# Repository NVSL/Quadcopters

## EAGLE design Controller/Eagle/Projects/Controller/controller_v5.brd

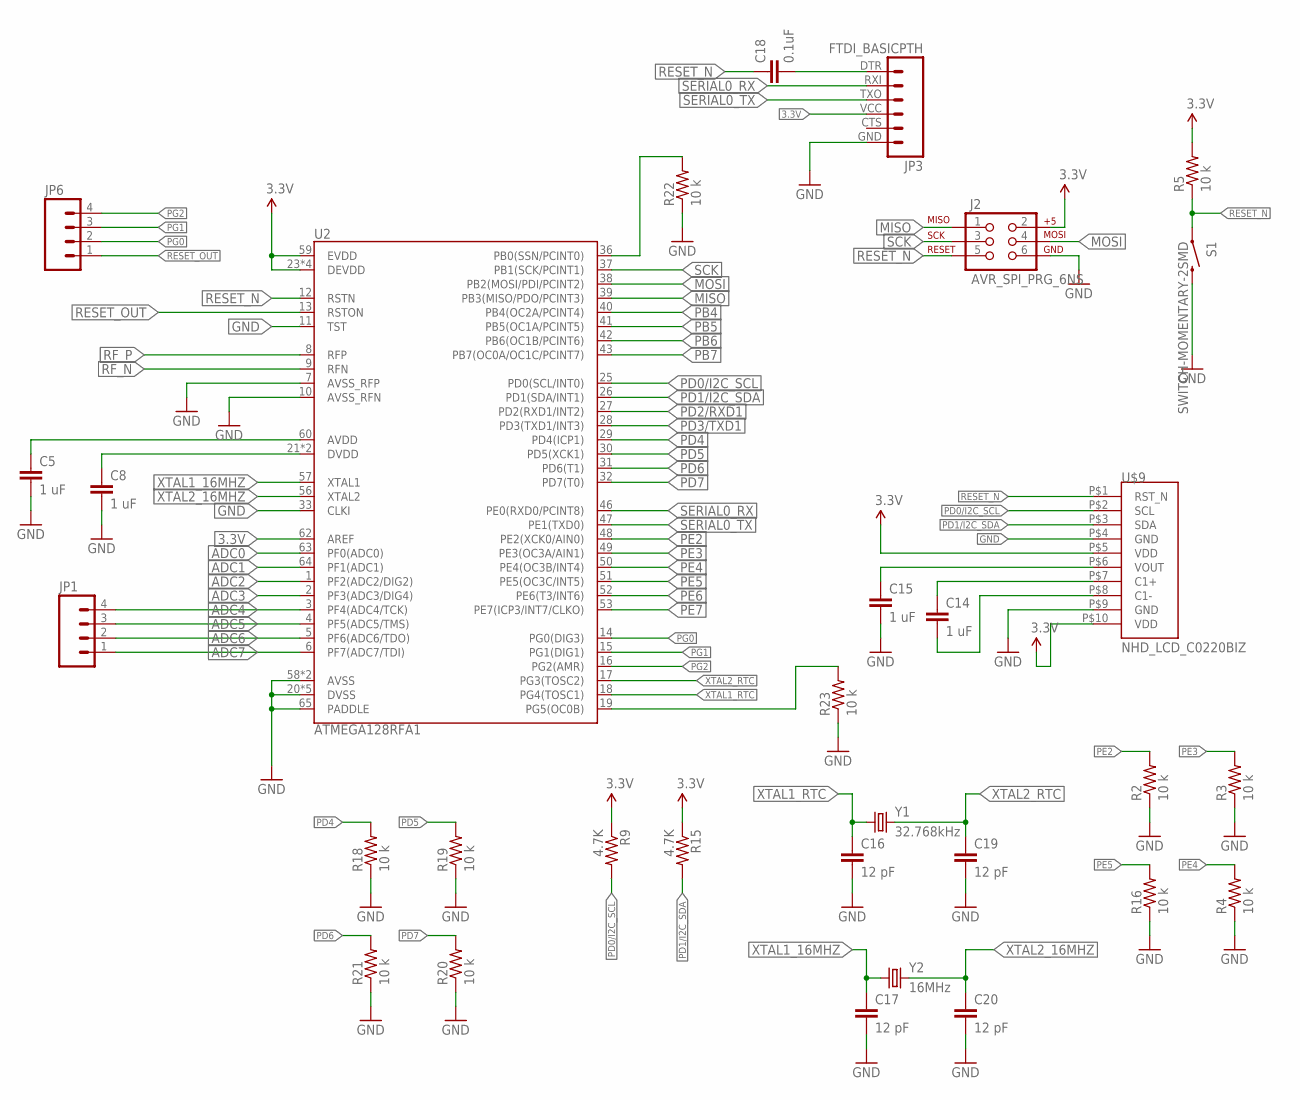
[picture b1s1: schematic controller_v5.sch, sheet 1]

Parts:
C5, C8, C14, C15: 1 uF; 0805
C16, C17, C19, C20: 12 pF; 0805
C18: 0.1uF; 0805
J2: AVR_SPI_PRG_6NS; 2X3-NS
JP1, JP6: M04PTH; 1X04
JP3: FTDI_BASICPTH; FTDI_BASIC
R2, R3, R4, R5, R16, R18, R19, R20, R21, R22, R23: 10 k; 0805
R9, R15: 4.7K; 0805
S1: SWITCH-MOMENTARY-2SMD; TACTILE_SWITCH_SMD
U2: ATMEGA128RFA1; QFN-64
U$9: NHD_LCD_C0220BIZ; 1X08-2MMPTH-LCD
Y1: 32.768kHz; CRYSTAL-32KHZ-SMD
Y2: 16MHz; CRYSTAL-SMD-5X3

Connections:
ADC0: U2.63 (PF0(ADC0)); also elsewhere on the board
ADC1: U2.64 (PF1(ADC1)); also elsewhere on the board
ADC2: U2.1 (PF2(ADC2/DIG2)); also elsewhere on the board
ADC3: U2.2 (PF3(ADC3/DIG4)); also elsewhere on the board
ADC4: JP1.4, U2.3 (PF4(ADC4/TCK))
ADC5: JP1.3, U2.4 (PF5(ADC5/TMS))
ADC6: JP1.2, U2.5 (PF6(ADC6/TDO))
ADC7: JP1.1, U2.6 (PF7(ADC7/TDI))
GND: C5.2, C8.2, C15.2, C16.2, C17.2, C19.2, C20.2, J2.6, JP3.GND (6), R2.1, R3.1, R4.1, R16.1, R18.1, R19.1, R20.1, R21.1, R22.1, R23.1, S1.3 (2), U2.7 (AVSS_RFP), U2.10 (AVSS_RFN), U2.11 (TST), U2.20 (DVSS), U2.24 (DVSS), U2.33 (CLKI), U2.35 (DVSS), U2.45 (DVSS), U2.55 (DVSS), U2.58 (AVSS), U2.61 (AVSS), U2.65 (PADDLE), U$9.P$4 (GND), U$9.P$9 (GND); also elsewhere on the board
MISO: J2.1, U2.39 (PB3(MISO/PDO/PCINT3))
MOSI: J2.4, U2.38 (PB2(MOSI/PDI/PCINT2))
unnamed: C18.2, JP3.DTR (1)
unnamed: C14.1, U$9.P$7 (C1+)
unnamed: C5.1, U2.60 (AVDD)
unnamed: C8.1, U2.21 (DVDD), U2.22 (DVDD)
unnamed: C14.2, U$9.P$8 (C1-)
PB0: R22.2, U2.36 (PB0(SSN/PCINT0))
PB1: R23.2, U2.19 (PG5(OC0B))
PB4: U2.40 (PB4(OC2A/PCINT4)); also elsewhere on the board
PB5: U2.41 (PB5(OC1A/PCINT5)); also elsewhere on the board
PB6: U2.42 (PB6(OC1B/PCINT6)); also elsewhere on the board
PB7: U2.43 (PB7(OC0A/OC1C/PCINT7)); also elsewhere on the board
PD0/I2C_SCL: R9.2, U2.25 (PD0(SCL/INT0)), U$9.P$2 (SCL)
PD1/I2C_SDA: R15.2, U2.26 (PD1(SDA/INT1)), U$9.P$3 (SDA)
PD2/RXD1: U2.27 (PD2(RXD1/INT2)); also elsewhere on the board
PD3/TXD1: U2.28 (PD3(TXD1/INT3)); also elsewhere on the board
PD4: R18.2, U2.29 (PD4(ICP1))
PD5: R19.2, U2.30 (PD5(XCK1))
PD6: R21.2, U2.31 (PD6(T1))
PD7: R20.2, U2.32 (PD7(T0))
PE2: R2.2, U2.48 (PE2(XCK0/AIN0))
PE3: R3.2, U2.49 (PE3(OC3A/AIN1))
PE4: R4.2, U2.50 (PE4(OC3B/INT4))
PE5: R16.2, U2.51 (PE5(OC3C/INT5))
PE6: U2.52 (PE6(T3/INT6)); also elsewhere on the board
PE7: U2.53 (PE7(ICP3/INT7/CLKO)); also elsewhere on the board
PG0: JP6.2, U2.14 (PG0(DIG3))
PG1: JP6.3, U2.15 (PG1(DIG1))
PG2: JP6.4, U2.16 (PG2(AMR))
RESET_N: C18.1, J2.5, R5.1, S1.1, U2.12 (RSTN), U$9.P$1 (RST_N)
RESET_OUT: JP6.1, U2.13 (RSTON)
RF_N: U2.9 (RFN); also elsewhere on the board
RF_P: U2.8 (RFP); also elsewhere on the board
SCK: J2.3, U2.37 (PB1(SCK/PCINT1))
SERIAL0_RX: JP3.RXI (2), U2.46 (PE0(RXD0/PCINT8))
SERIAL0_TX: JP3.TXO (3), U2.47 (PE1(TXD0))
VOUT: C15.1, U$9.P$6 (VOUT)
XTAL1_16MHZ: C17.1, U2.57 (XTAL1), Y2.1
XTAL1_RTC: C16.1, U2.18 (PG4(TOSC1)), Y1.X1 (1)
XTAL2_16MHZ: C20.1, U2.56 (XTAL2), Y2.3 (2)
XTAL2_RTC: C19.1, U2.17 (PG3(TOSC2)), Y1.X2 (2)

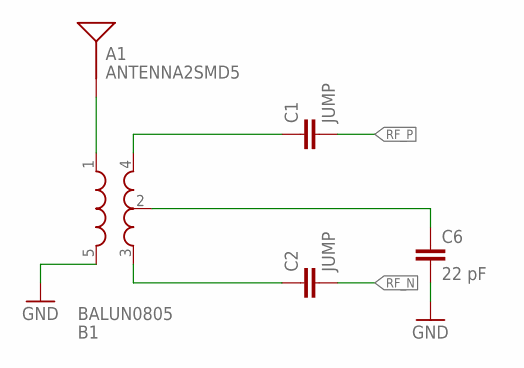
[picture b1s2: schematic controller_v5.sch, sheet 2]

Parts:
A1: ANTENNA2SMD5; ANTENNA-CHIP5
B1: BALUN0805; BALUN
C1, C2: JUMP; 0805
C6: 22 pF; 0805

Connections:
GND: B1.5 (GND), C6.2; also elsewhere on the board
unnamed: B1.4 (OUT1), C1.1
unnamed: B1.3 (OUT2), C2.1
unnamed: B1.2 (GND), C6.1
unnamed: A1.FEED, B1.1 (IN)
RF_N: C2.2; also elsewhere on the board
RF_P: C1.2; also elsewhere on the board

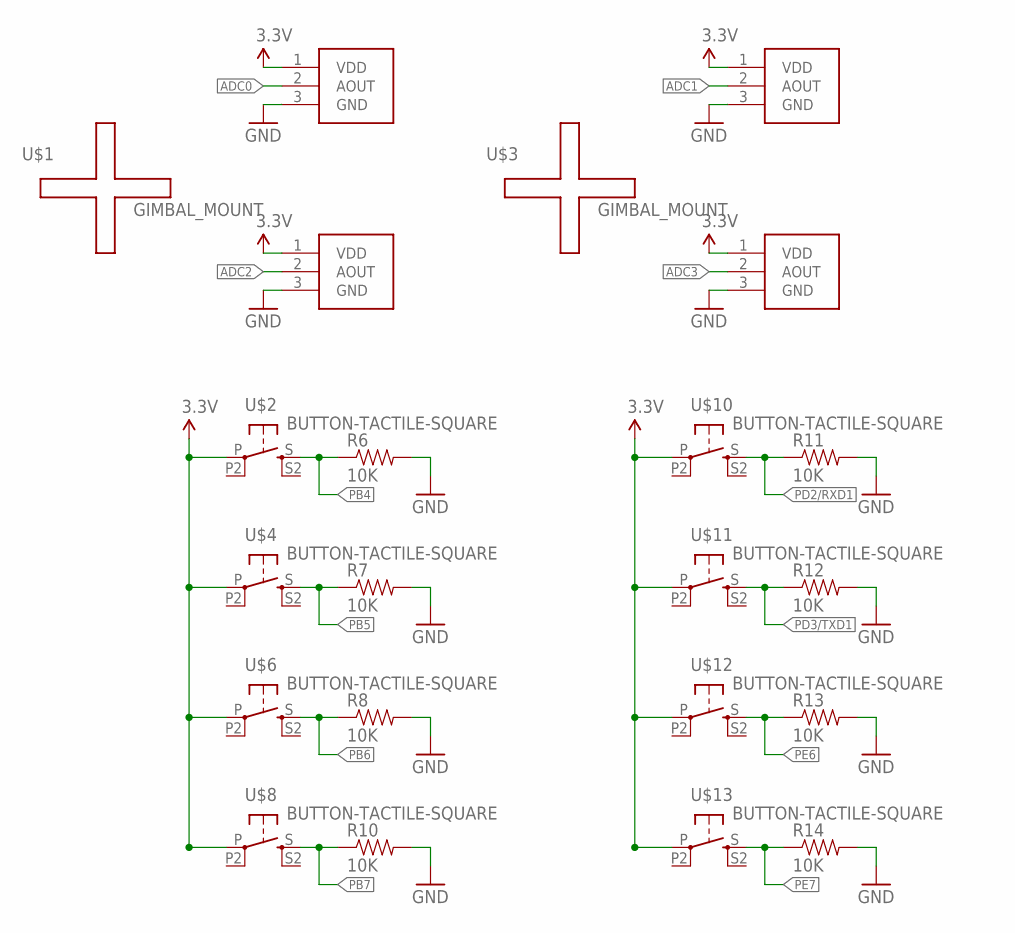
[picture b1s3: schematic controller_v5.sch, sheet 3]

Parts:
J3, J4, J5, J6: GIMBAL_3PIN; JST-3-PTH
R6, R7, R8, R10, R11, R12, R13, R14: 10K; 0805
U$1, U$3: GIMBAL_MOUNT; GIMBAL_FOOTPRINT
U$2, U$4, U$6, U$8, U$10, U$11, U$12, U$13: BUTTON-TACTILE-SQUARE; BUTTON-TACTILE-SQUARE-ADAFRUIT1010

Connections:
ADC0: J6.2 (AOUT); also elsewhere on the board
ADC1: J3.2 (AOUT); also elsewhere on the board
ADC2: J5.2 (AOUT); also elsewhere on the board
ADC3: J4.2 (AOUT); also elsewhere on the board
GND: J3.3 (GND), J4.3 (GND), J5.3 (GND), J6.3 (GND), R6.2, R7.2, R8.2, R10.2, R11.2, R12.2, R13.2, R14.2; also elsewhere on the board
PB4: R6.1, U$2.S; also elsewhere on the board
PB5: R7.1, U$4.S; also elsewhere on the board
PB6: R8.1, U$6.S; also elsewhere on the board
PB7: R10.1, U$8.S; also elsewhere on the board
PD2/RXD1: R11.1, U$10.S; also elsewhere on the board
PD3/TXD1: R12.1, U$11.S; also elsewhere on the board
PE6: R13.1, U$12.S; also elsewhere on the board
PE7: R14.1, U$13.S; also elsewhere on the board

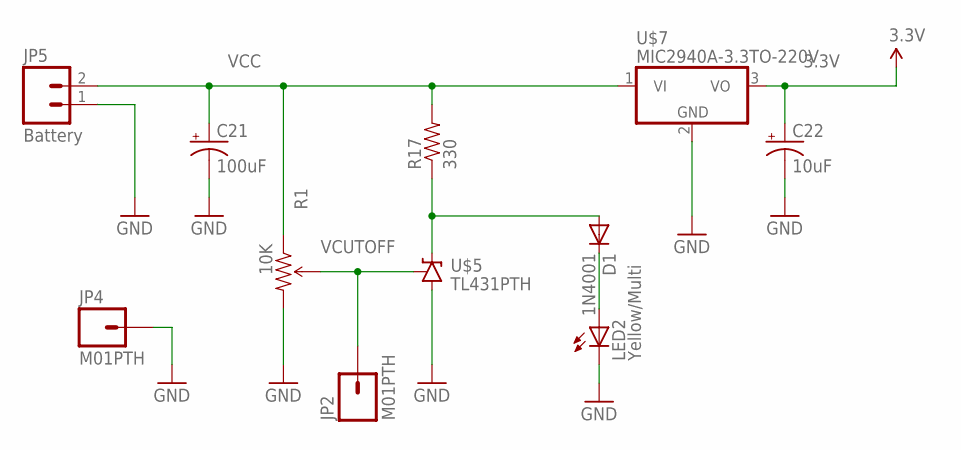
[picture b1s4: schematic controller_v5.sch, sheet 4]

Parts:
C21: 100uF; E3,5-8
C22: 10uF; E2,5-5
D1: 1N4001; DO41-10
JP2, JP4: M01PTH; 1X01
JP5: Battery; 1X02
LED2: Yellow/Multi; LED5MM
R1: 10K; 3386U
R17: 330; AXIAL-0.3
U$5: TL431PTH; TO-92
U$7: MIC2940A-3.3TO-220V; TO-220V

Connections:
GND: C21.-, C22.-, JP4.1, JP5.1, LED2.K (C), R1.3 (CW), U$5.2 (A), U$7.2 (GND); also elsewhere on the board
unnamed: D1.A, R17.P$1 (1), U$5.3 (C)
unnamed: D1.C, LED2.A
VCC: C21.+, JP5.2, R1.1 (CCW), R17.P$2 (2), U$7.1 (VI)
VCUTOFF: JP2.1, R1.2 (WIPER), U$5.1 (R)

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
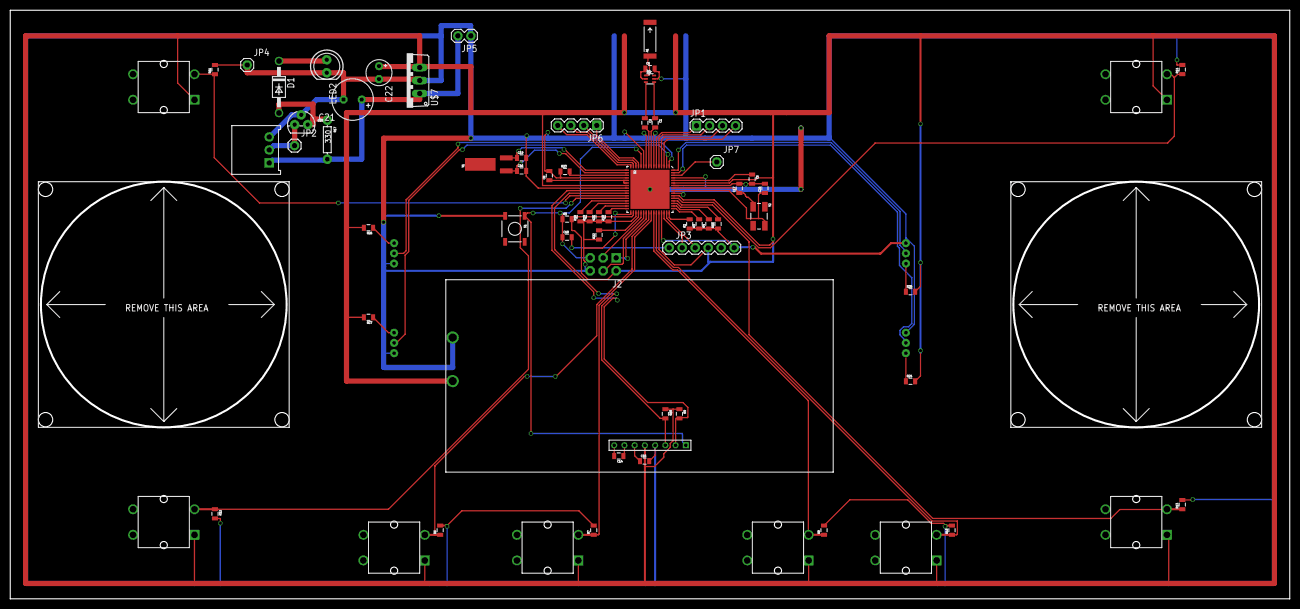
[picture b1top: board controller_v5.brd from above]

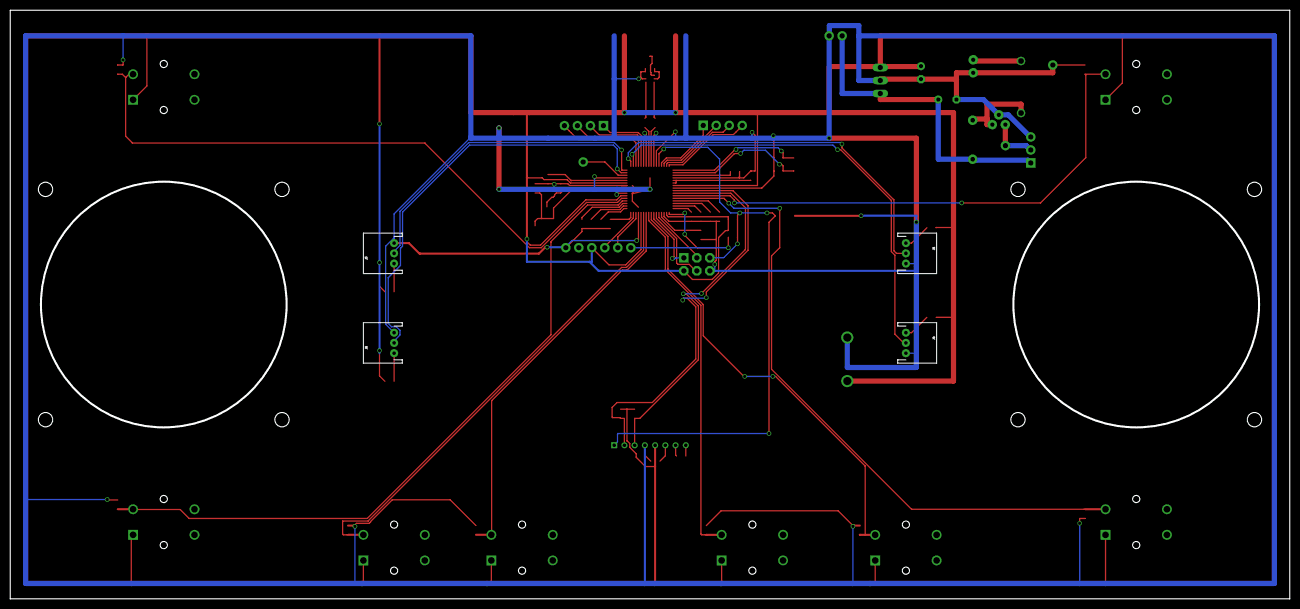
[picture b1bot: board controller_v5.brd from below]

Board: 2 copper layers, 250.0 x 115.0 mm, 74 parts (4 on the bottom side), 65 nets.

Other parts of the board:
JP7: M01PTH; 1X01
R24, R25, R26, R27: 5K; 0805

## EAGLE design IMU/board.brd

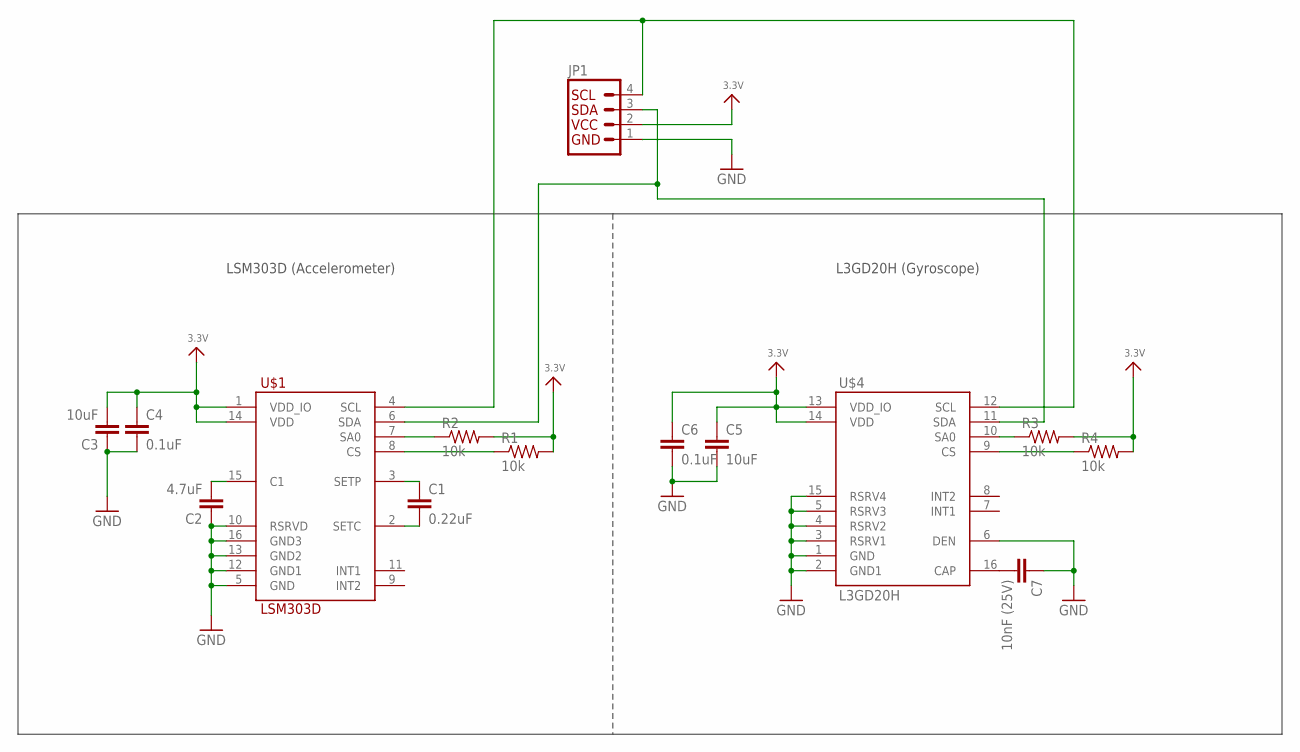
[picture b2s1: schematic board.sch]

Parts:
C1: 0.22uF; 0805
C2: 4.7uF; 0805
C3, C5: 10uF; 0805
C4, C6: 0.1uF; 0805
C7: 10nF (25V); 0805
JP1: I2C_STANDARD; 1X04
R1, R2, R3, R4: 10k; 0805
U$1: LSM303D; LGA16_3X3MM
U$4: L3GD20H; LGA16_3X3MM

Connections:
3.3V: C3.2, C4.1, C5.1, C6.1, JP1.2, R1.2, R2.2, R3.2, R4.2, U$1.1 (VDD_IO), U$1.14 (VDD), U$4.13 (VDD_IO), U$4.14 (VDD)
GND: C2.1, C3.1, C4.2, C5.2, C6.2, C7.1, JP1.1, U$1.5 (GND), U$1.10 (RSRVD), U$1.12 (GND1), U$1.13 (GND2), U$1.16 (GND3), U$4.1 (GND), U$4.2 (GND1), U$4.3 (RSRV1), U$4.4 (RSRV2), U$4.5 (RSRV3), U$4.6 (DEN), U$4.15 (RSRV4)
unnamed: C1.1, U$1.3 (SETP)
unnamed: C1.2, U$1.2 (SETC)
unnamed: R1.1, U$1.8 (CS)
unnamed: R2.1, U$1.7 (SA0)
unnamed: C2.2, U$1.15 (C1)
unnamed: R3.1, U$4.10 (SA0)
unnamed: R4.1, U$4.9 (CS)
unnamed: C7.2, U$4.16 (CAP)
unnamed: JP1.4, U$1.4 (SCL), U$4.12 (SCL)
unnamed: JP1.3, U$1.6 (SDA), U$4.11 (SDA)

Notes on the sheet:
LSM303D (Accelerometer)
L3GD20H (Gyroscope)

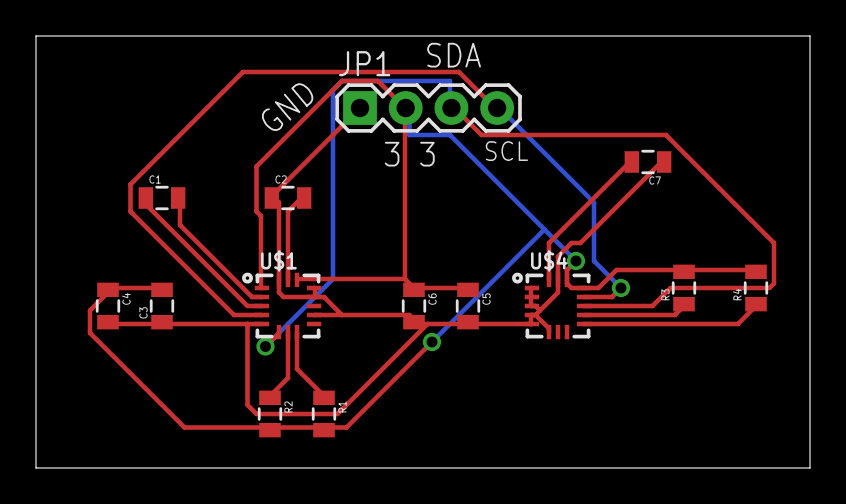
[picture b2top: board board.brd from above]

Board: 2 copper layers, 43.0 x 24.0 mm, 14 parts (0 on the bottom side), 12 nets.

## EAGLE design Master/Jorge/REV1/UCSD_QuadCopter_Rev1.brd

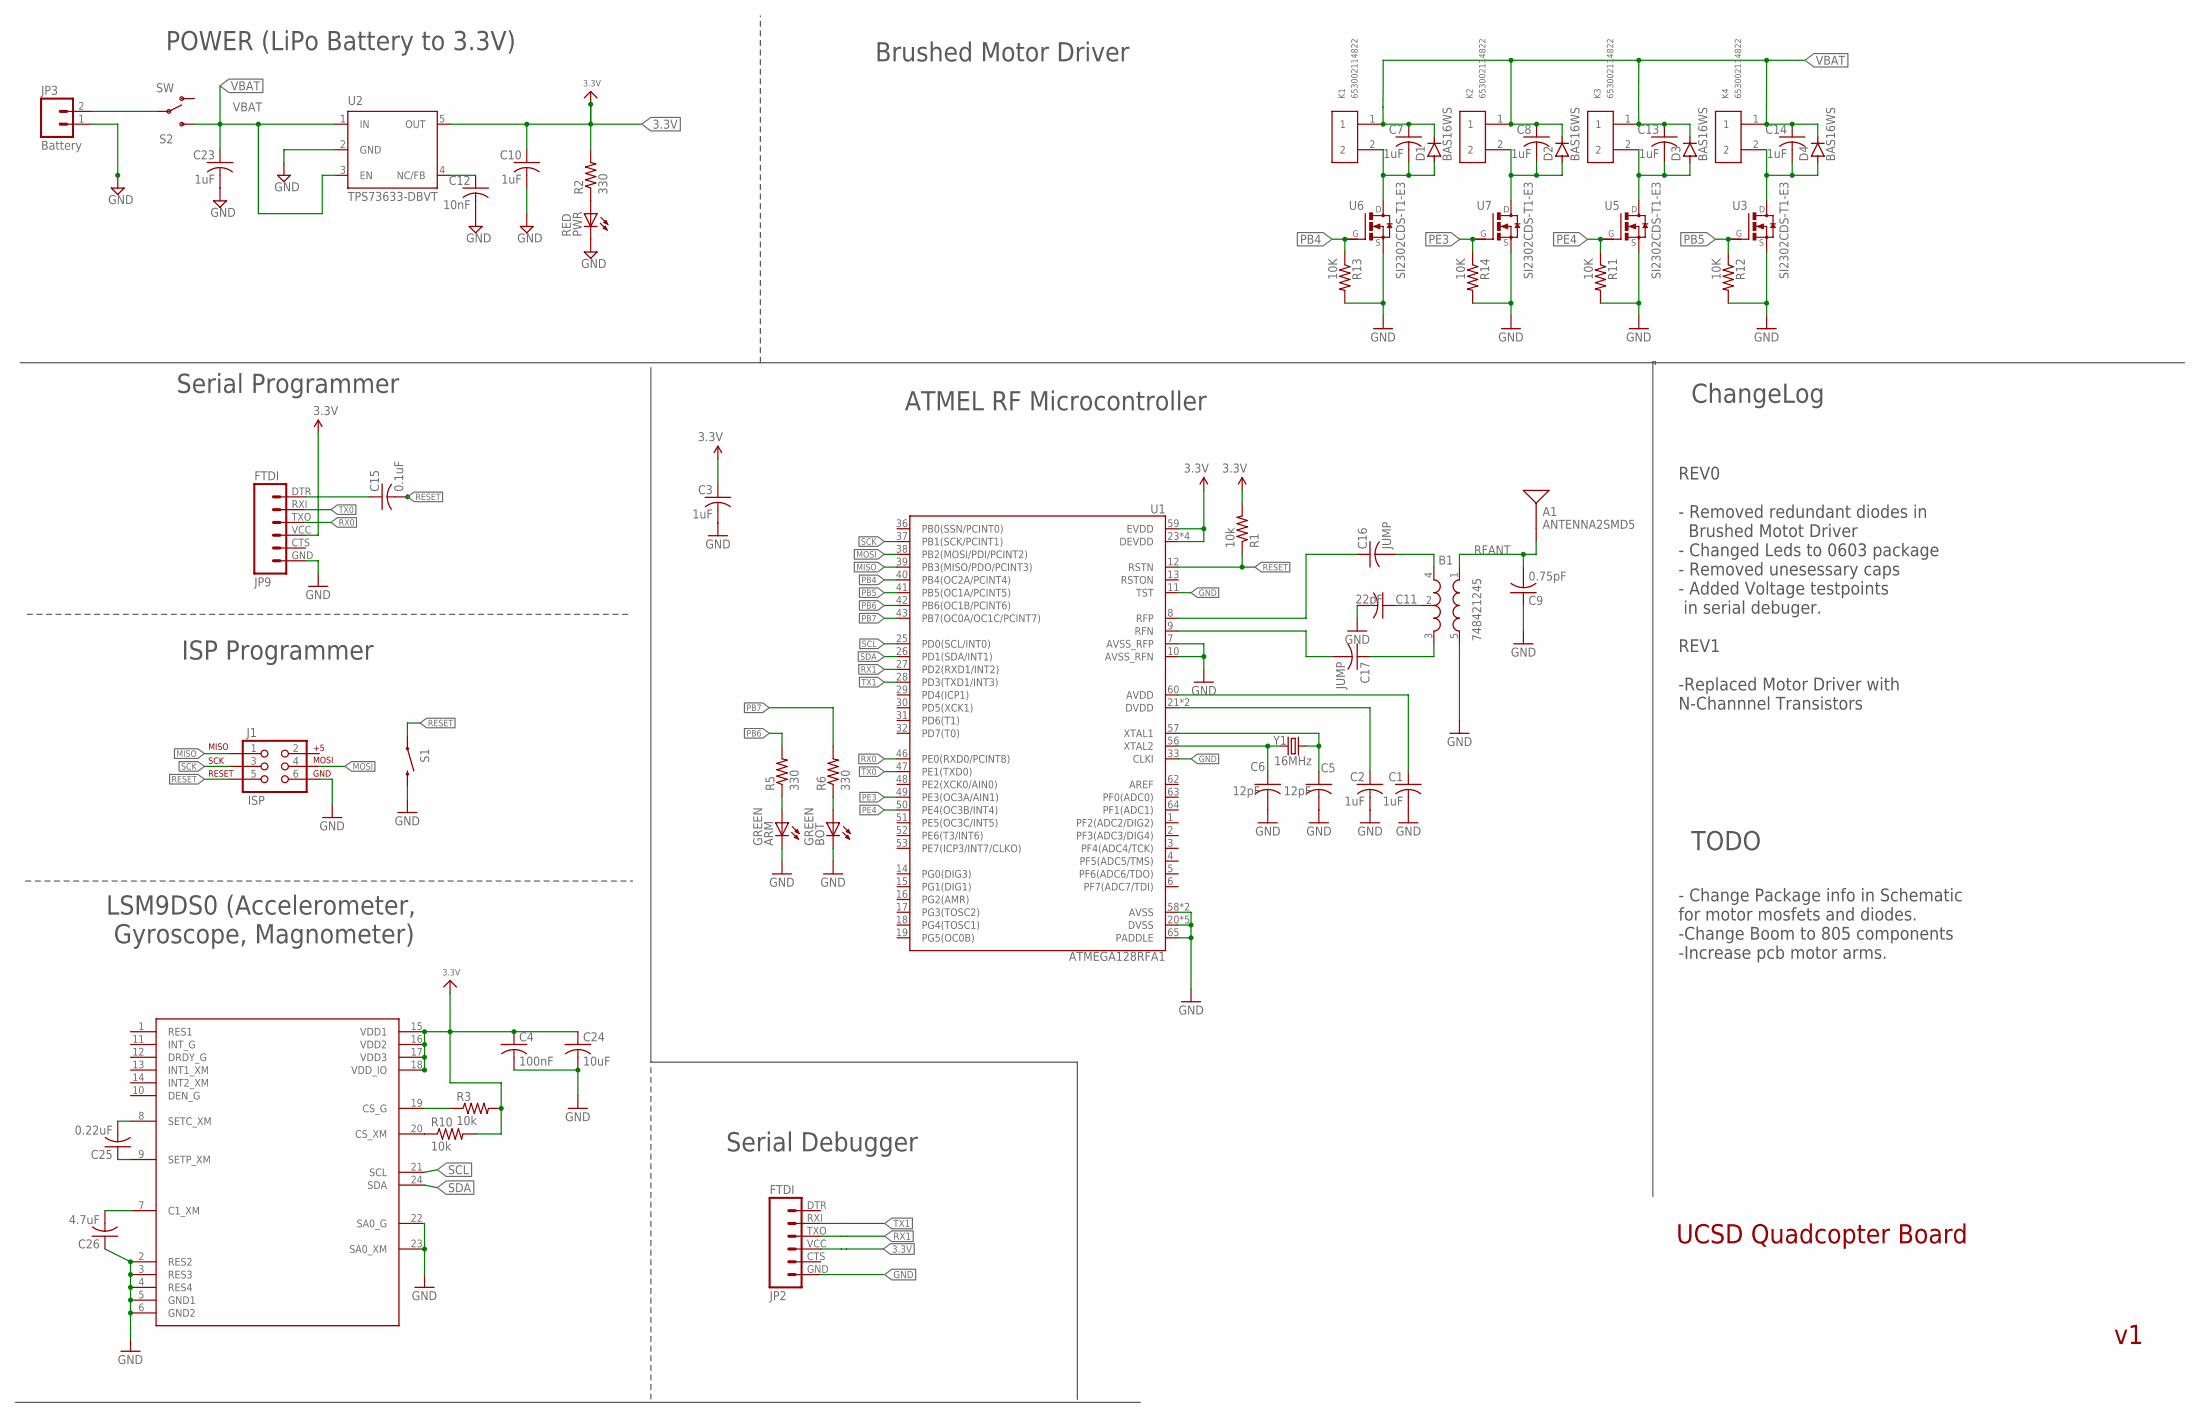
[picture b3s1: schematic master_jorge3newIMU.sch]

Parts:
A1: ANTENNA2SMD5; ANTENNA-CHIP5
ARM: GREEN; CHIP-LED0805
B1: 748421245; BALUN
BOT: GREEN; CHIP-LED0805
C1, C2, C3, C7, C8, C10, C13, C14, C23: 1uF; C0805
C4: 100nF; C0805
C5, C6: 12pF; C0805
C9: 0.75pF; C0805
C11: 22pF; C0805
C12: 10nF; C0805
C15: 0.1uF; C0805
C16, C17: JUMP; C0805
C24: 10uF; C0805
C25: 0.22uF; C0805
C26: 4.7uF; C0805
D1, D2, D3, D4: BAS16WS; SOD323_ST
J1: ISP; 2X3-NS
JP2, JP9: FTDI; FTDI_BASIC
JP3: Battery; 1X02
K1, K2, K3, K4: 653002114822
PWR: RED; CHIP-LED0805
R1, R3, R10: 10k; R0805
R2, R5, R6: 330; R0805
R11, R12, R13, R14: 10K; R0805
S1: SWITCH-MOMENTARY-2SMD; TACTILE_SWITCH_SMD
S2: SW; SWITCH-SPDT
U1: ATMEGA128RFA1; QFN-64
U2: TPS73633-DBVT; SOT23-DBV
U3, U5, U6, U7: SI2302CDS-T1-E3; SOT95P237X112-3N
U4: LSM9DS0; LGA-24
Y1: 16MHz; CRYSTAL-SMD-5X3

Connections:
3.3V: C3.1, C4.1, C10.1, C24.1, JP2.VCC (4), JP9.VCC (4), R1.2, R2.2, R3.2, R10.2, U1.23 (DEVDD), U1.34 (DEVDD), U1.44 (DEVDD), U1.54 (DEVDD), U1.59 (EVDD), U2.5 (OUT), U4.15 (VDD1), U4.16 (VDD2), U4.17 (VDD3), U4.18 (VDD_IO)
AVDD: C1.1, U1.60 (AVDD)
DTR: C15.1, JP9.DTR (1)
DVDD: C2.1, U1.21 (DVDD), U1.22 (DVDD)
GND: ARM.C, B1.5 (GND), BOT.C, C1.2, C2.2, C3.2, C4.2, C5.2, C6.2, C9.1, C10.2, C11.2, C12.2, C23.2, C24.2, C26.1, J1.6, JP2.GND (6), JP3.1, JP9.GND (6), PWR.C, R11.2, R12.2, R13.2, R14.2, S1.3 (2), U1.7 (AVSS_RFP), U1.10 (AVSS_RFN), U1.11 (TST), U1.20 (DVSS), U1.24 (DVSS), U1.33 (CLKI), U1.35 (DVSS), U1.45 (DVSS), U1.55 (DVSS), U1.58 (AVSS), U1.61 (AVSS), U1.65 (PADDLE), U2.2 (GND), U3.2 (S), U4.2 (RES2), U4.3 (RES3), U4.4 (RES4), U4.5 (GND1), U4.6 (GND2), U4.22 (SA0_G), U4.23 (SA0_XM), U5.2 (S), U6.2 (S), U7.2 (S)
MISO: J1.1, U1.39 (PB3(MISO/PDO/PCINT3))
MOSI: J1.4, U1.38 (PB2(MOSI/PDI/PCINT2))
unnamed: C12.1, U2.4 (NC/FB)
unnamed: PWR.A, R2.1
unnamed: C5.1, U1.57 (XTAL1), Y1.3 (2)
unnamed: C6.1, U1.56 (XTAL2), Y1.1
unnamed: B1.2 (GND), C11.1
unnamed: ARM.A, R5.1
unnamed: B1.4 (OUT1), C16.2
unnamed: B1.3 (OUT2), C17.1
unnamed: BOT.A, R6.1
unnamed: JP3.2, S2.2
unnamed: C26.2, U4.7 (C1_XM)
unnamed: C25.2, U4.8 (SETC_XM)
unnamed: C25.1, U4.9 (SETP_XM)
unnamed: R3.1, U4.19 (CS_G)
unnamed: R10.1, U4.20 (CS_XM)
unnamed: C7.2, D1.A, K1.2, U6.3 (D)
unnamed: C8.2, D2.A, K2.2, U7.3 (D)
unnamed: C13.2, D3.A, K3.2, U5.3 (D)
unnamed: C14.2, D4.A, K4.2, U3.3 (D)
PB4: R13.1, U1.40 (PB4(OC2A/PCINT4)), U6.1 (G)
PB5: R12.1, U1.41 (PB5(OC1A/PCINT5)), U3.1 (G)
PB6: R5.2, U1.42 (PB6(OC1B/PCINT6))
PB7: R6.2, U1.43 (PB7(OC0A/OC1C/PCINT7))
PE3: R14.1, U1.49 (PE3(OC3A/AIN1)), U7.1 (G)
PE4: R11.1, U1.50 (PE4(OC3B/INT4)), U5.1 (G)
RESET: C15.2, J1.5, R1.1, S1.1, U1.12 (RSTN)
RFANT: A1.FEED, B1.1 (IN), C9.2
RFN: C17.2, U1.9 (RFN)
RFP: C16.1, U1.8 (RFP)
RX0: JP9.TXO (3), U1.46 (PE0(RXD0/PCINT8))
RX1: JP2.TXO (3), U1.27 (PD2(RXD1/INT2))
SCK: J1.3, U1.37 (PB1(SCK/PCINT1))
SCL: U1.25 (PD0(SCL/INT0)), U4.21 (SCL)
SDA: U1.26 (PD1(SDA/INT1)), U4.24 (SDA)
TX0: JP9.RXI (2), U1.47 (PE1(TXD0))
TX1: JP2.RXI (2), U1.28 (PD3(TXD1/INT3))
VBAT: C7.1, C8.1, C13.1, C14.1, C23.1, D1.C, D2.C, D3.C, D4.C, K1.1, K2.1, K3.1, K4.1, S2.3 (S), U2.1 (IN), U2.3 (EN)

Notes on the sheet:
LSM9DS0 (Accelerometer, Gyroscope, Magnometer)
POWER (LiPo Battery to 3.3V)
Brushed Motor Driver
UCSD Quadcopter Board
Serial Programmer
ISP Programmer
Serial Debugger
ATMEL RF Microcontroller
ChangeLog
REV0 - Removed redundant diodes in Brushed Motot Driver - Changed Leds to 0603 package - Removed unesessary caps - Added Voltage testpoints in serial debuger. REV1 -Replaced Motor Driver with N-Channnel Transistors
TODO
- Change Package info in Schematic for motor mosfets and diodes. -Change Boom to 805 components -Increase pcb motor arms.

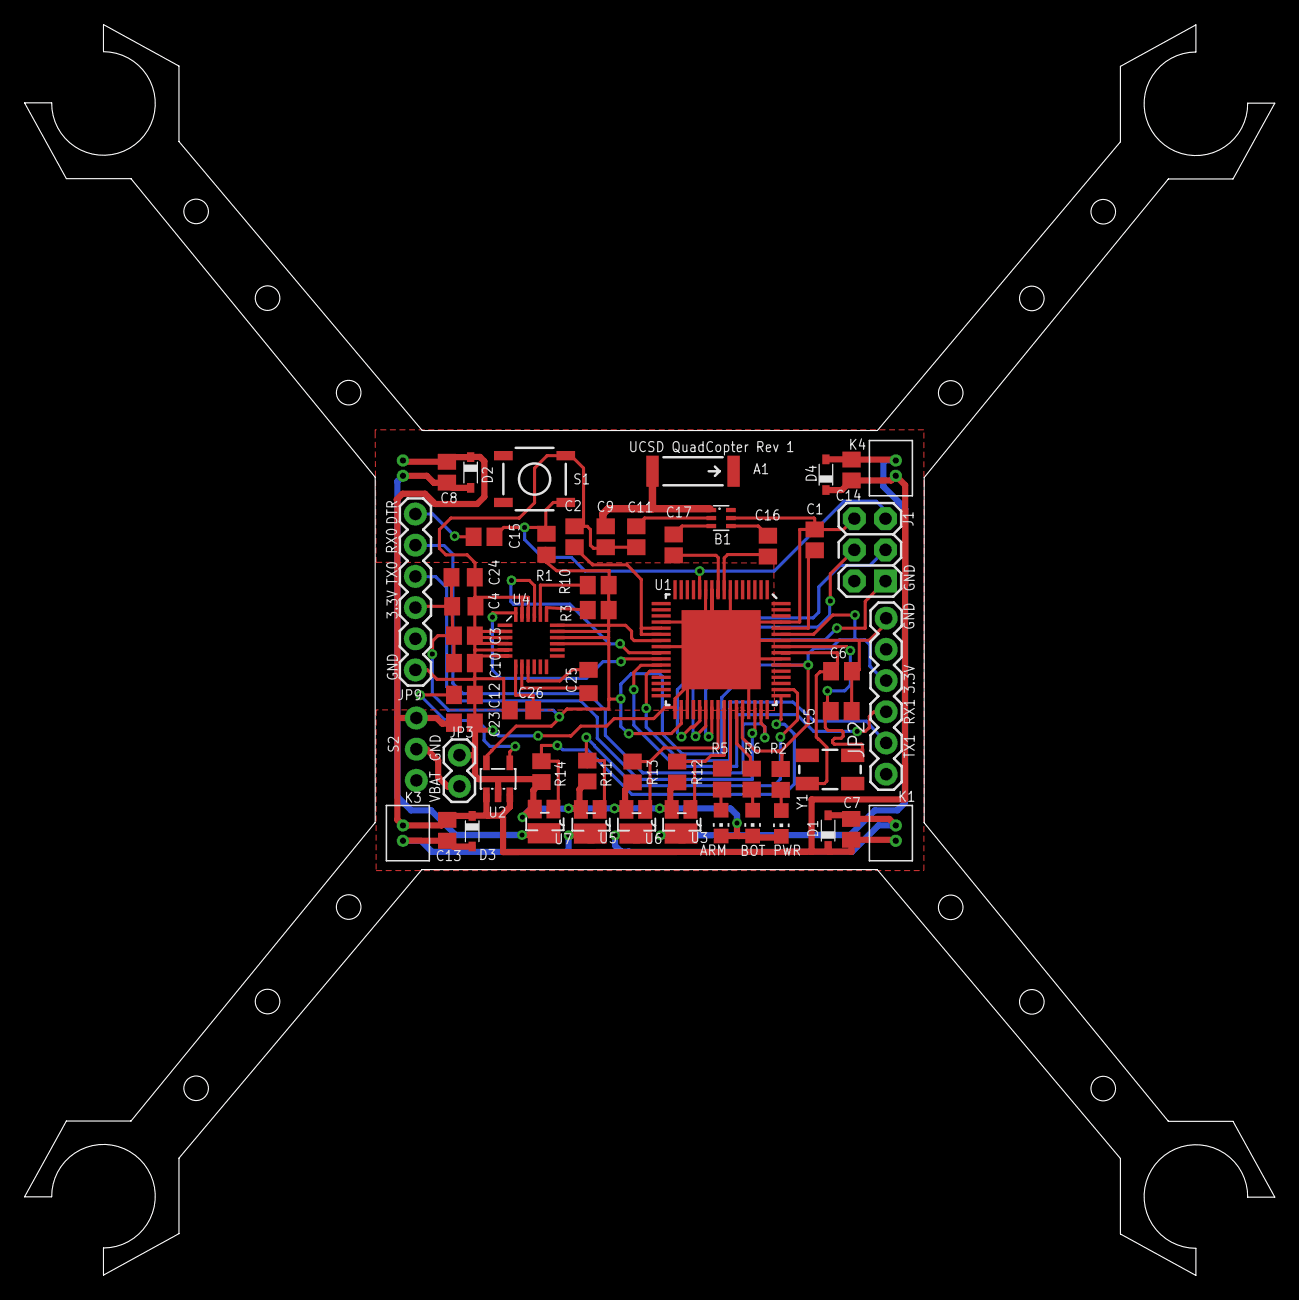
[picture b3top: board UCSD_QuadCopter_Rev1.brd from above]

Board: 2 copper layers, 101.8 x 101.9 mm, 58 parts (1 on the bottom side), 44 nets.

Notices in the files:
parts and their libraries:
SparkFun-Capacitors: Licensing: Creative Commons ShareAlike 4.0 International - https://creativecommons.org/licenses/by-sa/4.0
microbuilder: This work is placed in the public domain, and may be freely used for commercial and non-commercial work with the following conditions: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
